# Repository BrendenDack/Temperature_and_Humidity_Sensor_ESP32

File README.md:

# Temperature and Humidity Sensor using an ESP32

This project uses an esp32doit-devkit-v1 board, a DHT11 temperature and humidity sensor, and a LCD1602 16x2 LCD screen to display the sensor readings for the user.
The board also has a button for toggling between Farenheit and Celsius, and it hosts an internal HTTP server to displaying the readings on a local website.
There is an onboard Potentiometer that can be used to adjust the screen contrast, if you want to use a static resistor instead, I find around 8.2Kohm works best.

This project was developed in the Arduino IDE, and later imported into PlatformIO.

To get started with this project: 

## Hardware Setup

The circuit:
 * USB to ESP32 Dev Board
 * LCD RS pin to digital pin 32
 * LCD Enable pin to digital pin 33
 * LCD D4 pin to digital pin 25
 * LCD D5 pin to digital pin 26
 * LCD D6 pin to digital pin 27
 * LCD D7 pin to digital pin 14
 * LCD R/W pin to ground
 * LCD VSS pin to ground
 * LCD VCC pin to 5V
 * 10K potentiometer:
 * ends to +5V and ground
 * wiper to LCD VO pin (pin 3)
 * DHT11 VCC to 5V
 * DHT11 GND to GND
 * DHT11 DATA to pin 13
 * Button to pin 34 (REQUIRES 3.3V, 5V will not work)
 * 10Kohm pulldown resistor for button to ground

Here is a picture of the physical design on a breadboard. I have a power supply on one end that is only used to jump 5V to both power rails and the same effect can be had using jumper wires.
The Dev board has an onboard voltage regulator that accepts 5V, and has a 3.3V output that you can use to wire up the button. This way you do not have to supply both 5V and 3.3V manually.

Here is a picture of the website. It is made using very basic html, css, and js.

Inside /kicad_files contains the kicad schematic and pcb files. You can reference these for how the pcb is assembled, however the gpio connections in the schematic are not the same
as the connections defined in the code. This is because I changed the gpio pins for easier traces on the PCB design. If you're planning to build on a breadboard, use the pins defined in the code.

## Software Setup
Clone the repository into a working folder of your choosing.
Then open the project with PlatformIO. Verify that it compiles, then upload it to the ESP32 Dev Board.

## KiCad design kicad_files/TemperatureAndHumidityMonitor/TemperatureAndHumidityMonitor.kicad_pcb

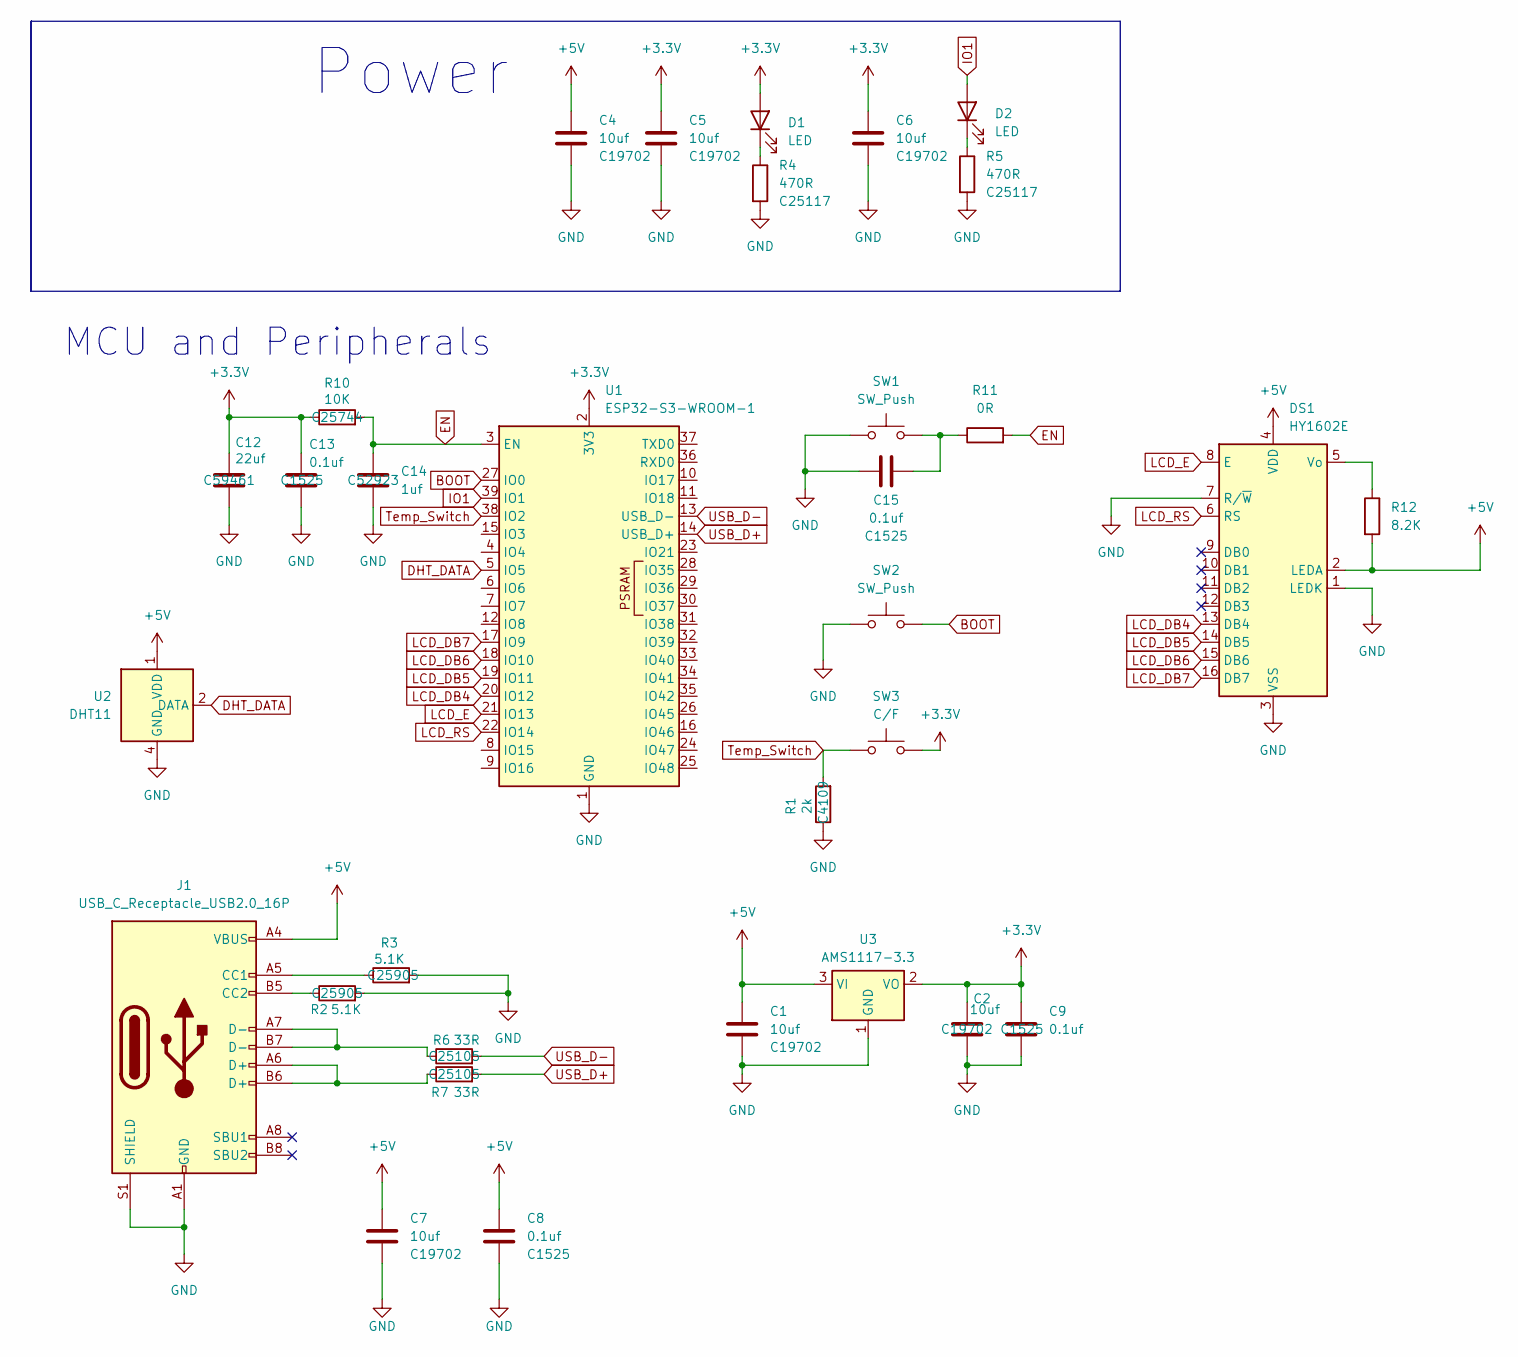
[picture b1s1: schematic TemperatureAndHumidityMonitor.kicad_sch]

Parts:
C1, C2, C4, C5, C6, C7: 10uf; C_0201_0603Metric; MNF PART NUMBER C19702
C8, C9, C13, C15: 0.1uf; C_0402_1005Metric; MNF PART NUMBER C1525
C12: 22uf; C_0201_0603Metric; MNF PART NUMBER C59461
C14: 1uf; C_0402_1005Metric; MNF PART NUMBER C52923
D1, D2: LED; LED_0201_0603Metric; MNF PART NUMBER C2286
DS1: HY1602E
J1: USB_C_Receptacle_USB2.0_16P; USB_C_Receptacle_G-Switch_GT-USB-7010ASV; MNF PART NUMBER C2988369
R1: 2k; R_0402_1005Metric; MNF PART NUMBER C4109
R2, R3: 5.1K; R_0402_1005Metric; MNF PART NUMBER C25905
R4, R5: 470R; R_0402_1005Metric; MNF PART NUMBER C25117
R6, R7: 33R; R_0402_1005Metric; MNF PART NUMBER C25105
R10: 10K; R_0402_1005Metric; MNF PART NUMBER C25744
R11: 0R; R_0402_1005Metric; MNF PART NUMBER C17168
R12: 8.2K; R_0201_0603Metric; MNF PART NUMBER C25981
SW1, SW2: SW_Push; SW_SPST_B3U-1000P; MNF PART NUMBER C720477
SW3: C/F; SW_SPST_B3U-1000P; MNF PART NUMBER C720477
U1: ESP32-S3-WROOM-1; MNF PART NUMBER C2913197
U2: DHT11; Aosong_DHT11_5.5x12.0_P2.54mm; MNF PART NUMBER C117051
U3: AMS1117-3.3; SOT-223-3_TabPin2; MNF PART NUMBER C6186

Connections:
+3.3V: C2.1, C5.1, C6.1, C9.1, C12.1, C13.1, D1.2 (A), R10.1, SW3.2, U1.2 (3V3), U3.2 (VO)
+5V: C1.1, C4.1, C7.1, C8.1, DS1.2 (LEDA), DS1.4 (VDD), J1.A4 (VBUS), J1.A9 (VBUS), J1.B4 (VBUS), J1.B9 (VBUS), R12.2, U2.1 (VDD), U3.3 (VI)
BOOT: SW2.2, U1.27 (IO0)
DHT_DATA: U1.5 (IO5), U2.2 (DATA)
EN: C14.1, R10.2, R11.2, U1.3 (EN)
GND: C1.2, C2.2, C4.2, C5.2, C6.2, C7.2, C8.2, C9.2, C12.2, C13.2, C14.2, C15.1, DS1.1 (LEDK), DS1.3 (VSS), DS1.7 (R/~W), J1.A1 (GND), J1.A12 (GND), J1.B1 (GND), J1.B12 (GND), J1.S1 (SHIELD), R1.1, R2.2, R3.2, R4.2, R5.2, SW1.1, SW2.1, U1.1 (GND), U1.40 (GND), U1.41 (GND), U2.4 (GND), U3.1 (GND)
IO1: D2.2 (A), U1.39 (IO1)
LCD_DB4: DS1.13 (DB4), U1.20 (IO12)
LCD_DB5: DS1.14 (DB5), U1.19 (IO11)
LCD_DB6: DS1.15 (DB6), U1.18 (IO10)
LCD_DB7: DS1.16 (DB7), U1.17 (IO9)
LCD_E: DS1.8 (E), U1.21 (IO13)
LCD_RS: DS1.6 (RS), U1.22 (IO14)
unnamed: C15.2, R11.1, SW1.2
unnamed: D1.1 (K), R4.1
unnamed: D2.1 (K), R5.1
unnamed: DS1.5 (Vo), R12.1
unnamed: J1.A5 (CC1), R3.1
unnamed: J1.B5 (CC2), R2.1
unnamed: J1.A6 (D+), J1.B6 (D+), R7.1
unnamed: J1.A7 (D-), J1.B7 (D-), R6.1
Temp_Switch: R1.2, SW3.1, U1.38 (IO2)
USB_D+: R7.2, U1.14 (USB_D+)
USB_D-: R6.2, U1.13 (USB_D-)

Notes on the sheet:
Power
MCU and Peripherals

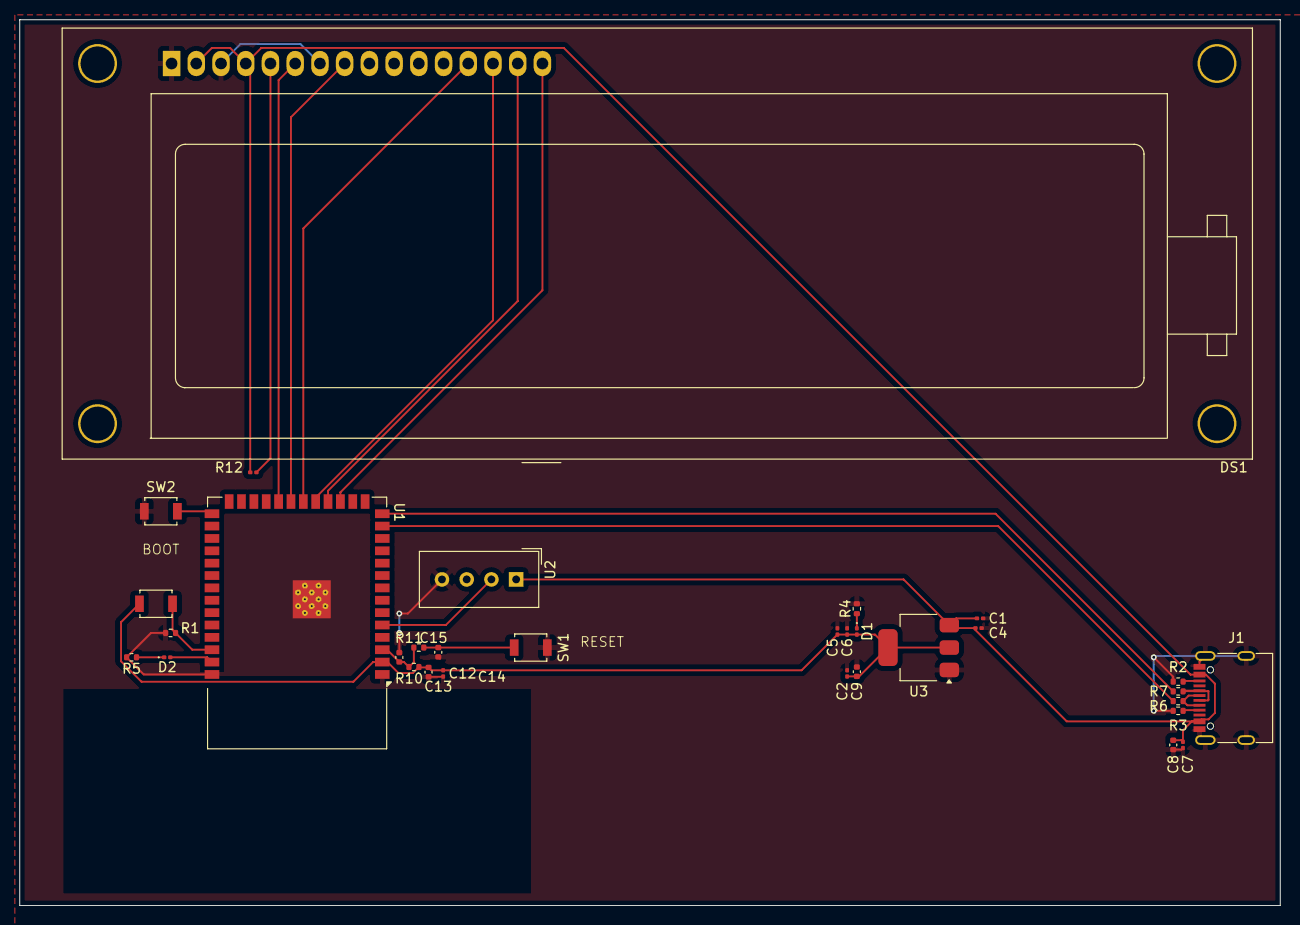
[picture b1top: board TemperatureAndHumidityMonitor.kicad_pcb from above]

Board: 2 copper layers, 129.5 x 91.0 mm, 32 parts (0 on the bottom side), 24 nets.

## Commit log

2025-07-21 removed secret_keys from tracking
2025-07-21 updated comment about WIFI SSID and Password to reflect it's new location
2025-07-21 changed platformio.ini to use only libraries in lib instead of external libraries from the arduino IDE
2025-07-21 removed comment about external library
2025-07-21 Added secret_keys_template.h so users have an example file to work with
2025-07-21 Added readme with instructions and basic summary
2025-07-21 Added image of the website, and added text for both images
2025-07-21 Added code to make temp type (C or F) choice reflect on the website as well. Also added variable to platformio.ini to set the correct serial monitor rate.
